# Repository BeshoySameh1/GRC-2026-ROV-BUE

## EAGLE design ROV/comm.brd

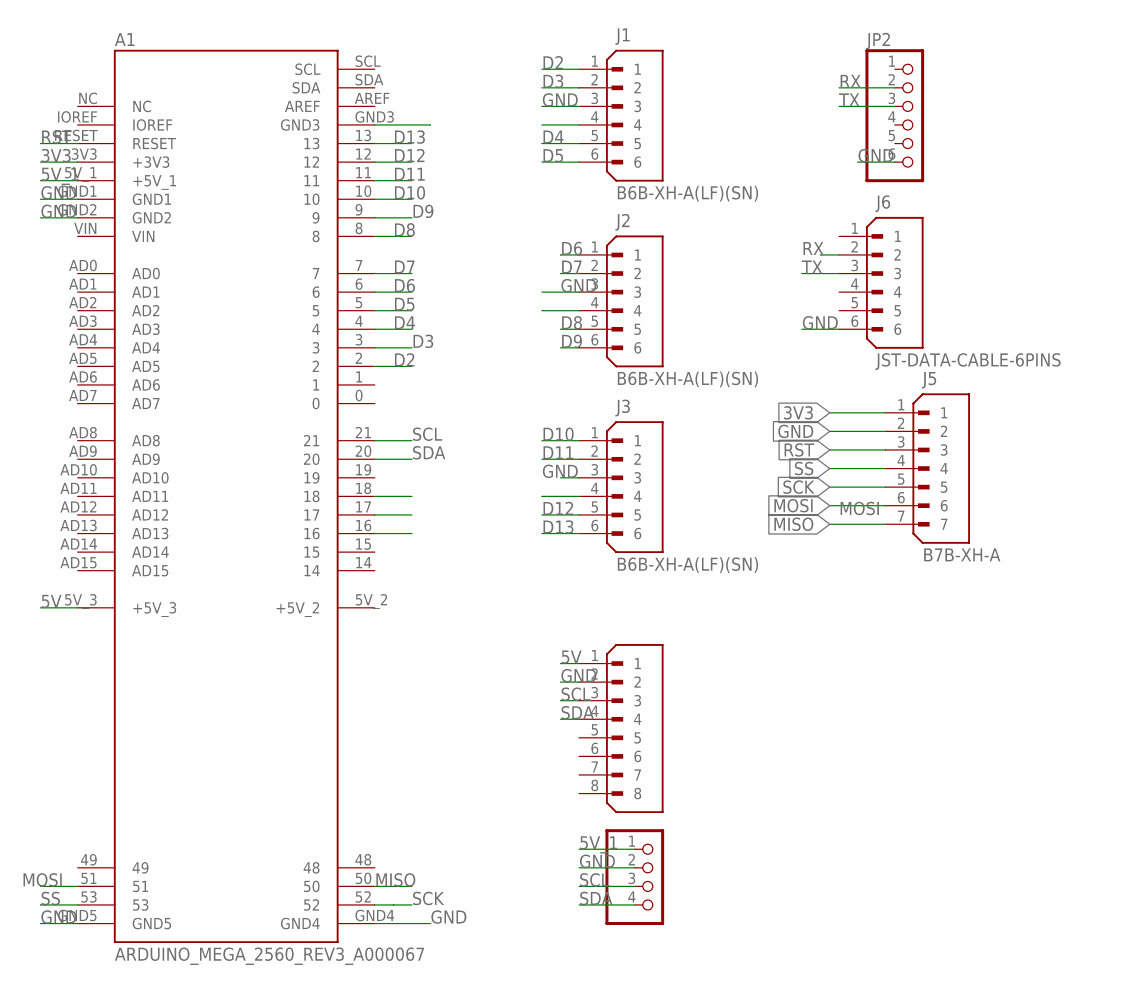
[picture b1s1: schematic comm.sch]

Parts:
A1: ARDUINO_MEGA_2560_REV3_A000067; ARDUINO_ARDUINO_MEGA_2560_REV3_A000067
J1, J2, J3: B6B-XH-A(LF)(SN); JST_B6B-XH-A(LF)(SN)
J4: B8B-XH-A(LF)(SN); JST_B8B-XH-A(LF)(SN)
J5: B7B-XH-A; JST_B7B-XH-A
J6: JST-DATA-CABLE-6PINS; JST_B6B-XH-A(LF)(SN)
JP1: PINHD-1X4; 1X04
JP2: PINHD-1X6; 1X06

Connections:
3V3: A1.3V3 (+3V3), J5.1
5V: A1.5V_3 (+5V_3), J4.1
5V_1: A1.5V_1 (+5V_1), JP1.1
D2: A1.2, J1.1
D3: A1.3, J1.2
D4: A1.4, J1.5
D5: A1.5, J1.6
D6: A1.6, J2.1
D7: A1.7, J2.2
D8: A1.8, J2.5
D9: A1.9, J2.6
D10: A1.10, J3.1
D11: A1.11, J3.2
D12: A1.12, J3.4, J3.5
D13: A1.13, J3.6
GND: A1.GND1, A1.GND2, A1.GND4, A1.GND5, J1.3, J2.3, J3.3, J4.2, J5.2, J6.6, JP1.2, JP2.6
MISO: A1.50, J5.7
MOSI: A1.51, J5.6
RST: A1.RESET, J5.3
RX: J6.2, JP2.2
SCK: A1.52, J5.5
SCL: A1.21, J4.3, JP1.3
SDA: A1.20, J4.4, JP1.4
SS: A1.53, J5.4
TX: J6.3, JP2.3

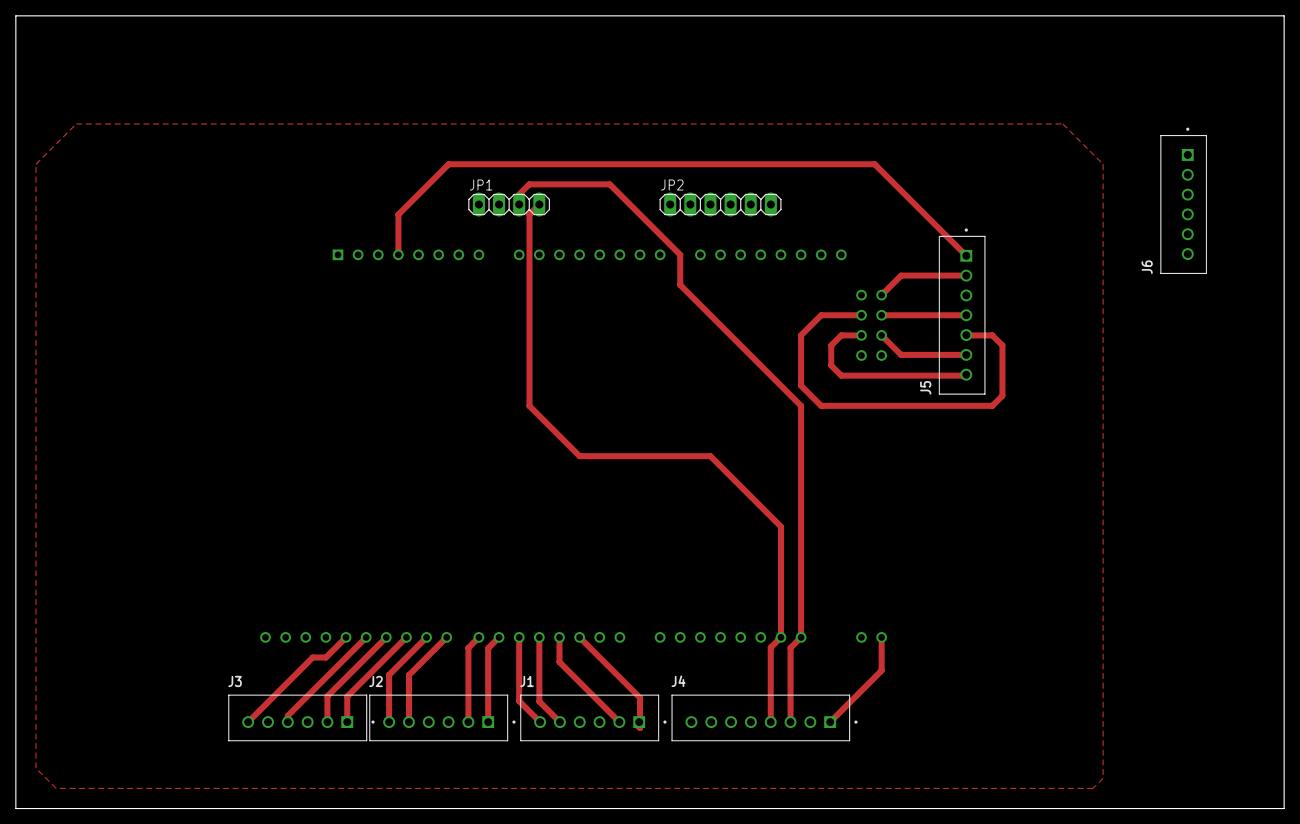
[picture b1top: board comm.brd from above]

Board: 2 copper layers, 160.0 x 100.0 mm, 9 parts (1 on the bottom side), 25 nets.

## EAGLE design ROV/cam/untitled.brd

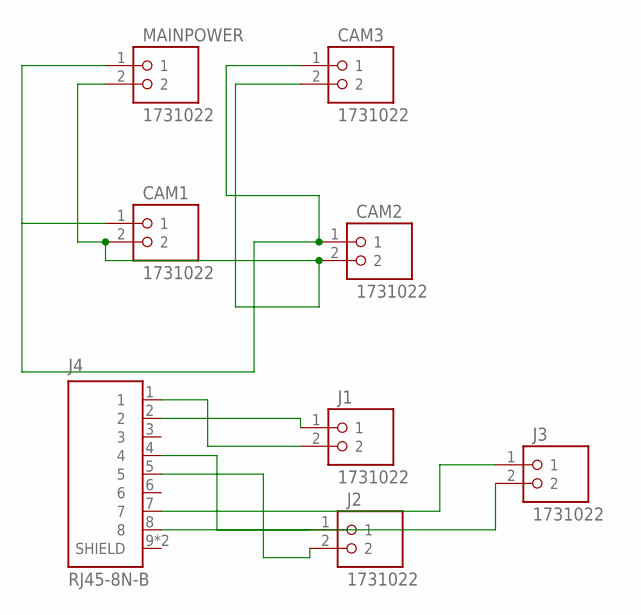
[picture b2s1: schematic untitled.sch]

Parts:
CAM1, CAM2, CAM3: 1731022; PHOENIX_1731022
J1, J2, J3: 1731022; PHOENIX_1731022
J4: RJ45-8N-B; TE_RJ45-8N-B
MAINPOWER: 1731022; PHOENIX_1731022

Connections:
12V: CAM1.1, CAM2.1, CAM3.1, MAINPOWER.1
GND: CAM1.2, CAM2.2, CAM3.2, MAINPOWER.2
unnamed: J1.1, J4.2
unnamed: J1.2, J4.1
unnamed: J2.1, J4.4
unnamed: J2.2, J4.5
unnamed: J3.1, J4.7
unnamed: J3.2, J4.8

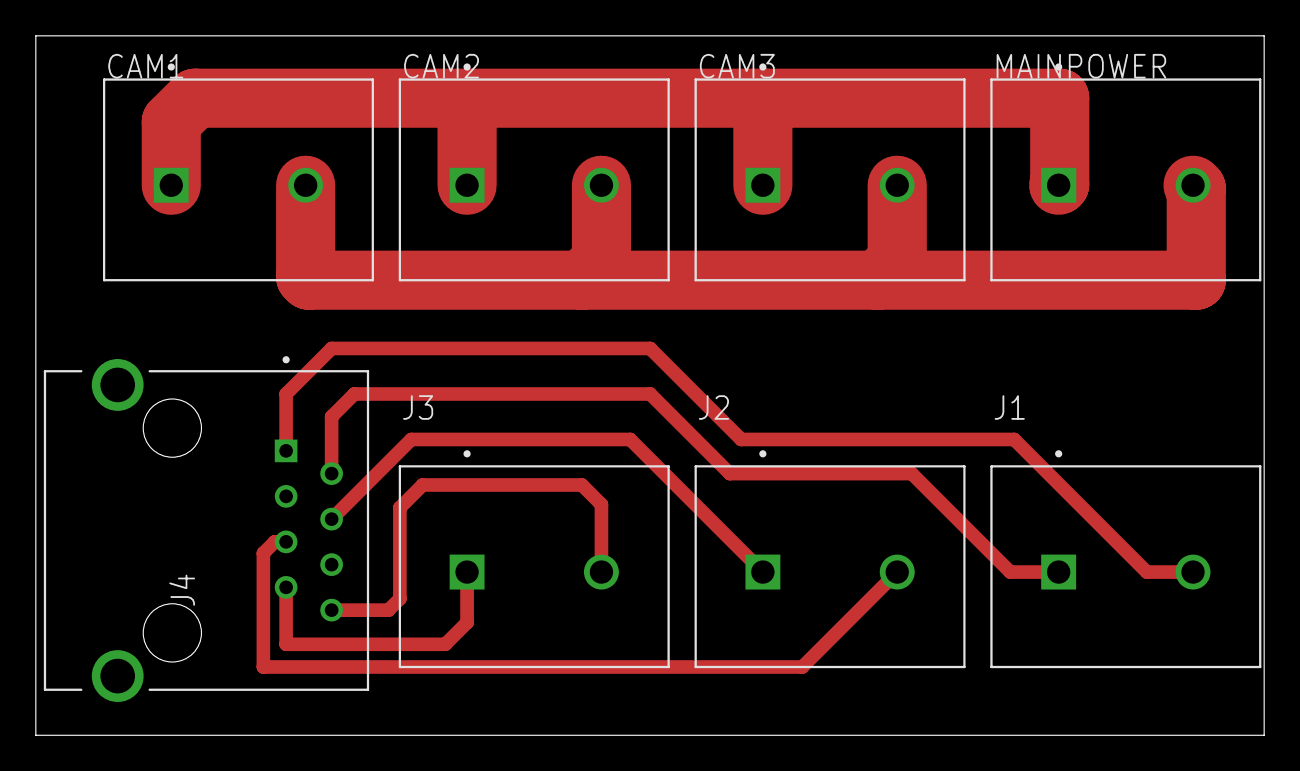
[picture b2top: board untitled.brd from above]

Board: 2 copper layers, 68.6 x 39.0 mm, 8 parts (0 on the bottom side), 8 nets.

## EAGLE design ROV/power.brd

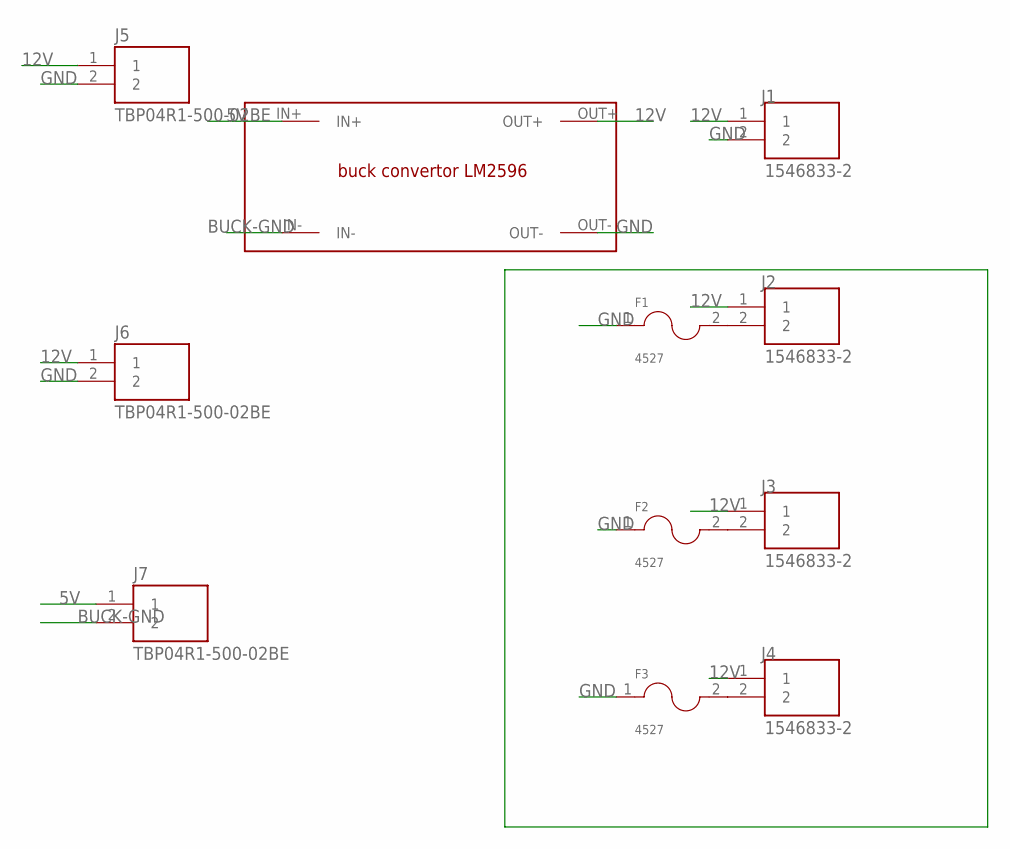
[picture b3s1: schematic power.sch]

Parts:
F1, F2, F3: 4527; FUSE_4527
J1, J2, J3, J4: 1546833-2; TE_1546833-2
J5, J6, J7: TBP04R1-500-02BE; CUI_TBP04R1-500-02BE
U$1: LM2596

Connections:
5V: J7.1, U$1.IN+
12V: J1.1, J2.1, J3.1, J4.1, J5.1, J6.1, U$1.OUT+
BUCK-GND: J7.2, U$1.IN-
GND: F1.1, F2.1, F3.1, J1.2, J5.2, J6.2, U$1.OUT-
unnamed: F1.2, J2.2
unnamed: F2.2, J3.2
unnamed: F3.2, J4.2

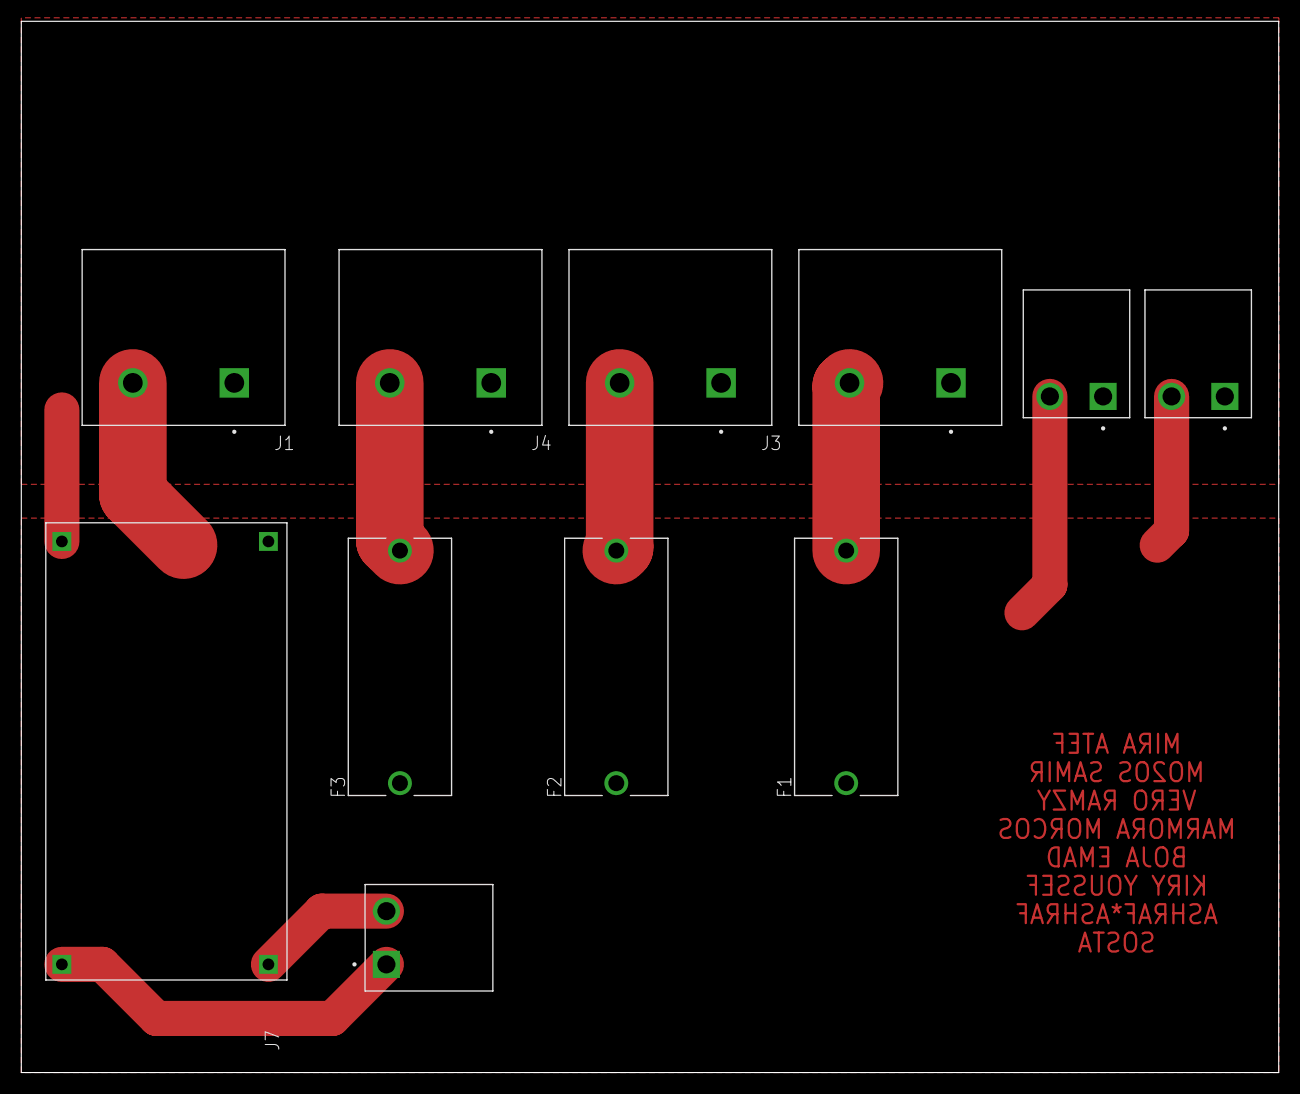
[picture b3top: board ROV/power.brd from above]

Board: 2 copper layers, 118.1 x 98.7 mm, 11 parts (0 on the bottom side), 7 nets.

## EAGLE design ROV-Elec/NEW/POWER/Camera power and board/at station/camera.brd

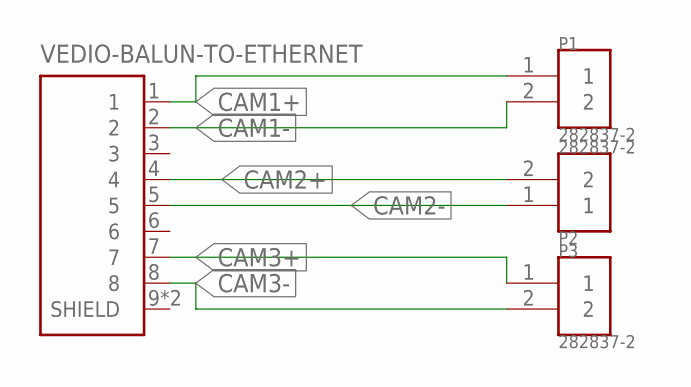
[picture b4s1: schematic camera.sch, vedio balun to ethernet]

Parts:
P1, P2, P3: 282837-2; TE_282837-2
VEDIO-BALUN-TO-ETHERNET: RJ45-8N-B; TE_RJ45-8N-B

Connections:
CAM1+: P1.1, VEDIO-BALUN-TO-ETHERNET.1
CAM1-: P1.2, VEDIO-BALUN-TO-ETHERNET.2
CAM2+: P2.2, VEDIO-BALUN-TO-ETHERNET.4
CAM2-: P2.1, VEDIO-BALUN-TO-ETHERNET.5
CAM3+: P3.1, VEDIO-BALUN-TO-ETHERNET.7
CAM3-: P3.2, VEDIO-BALUN-TO-ETHERNET.8

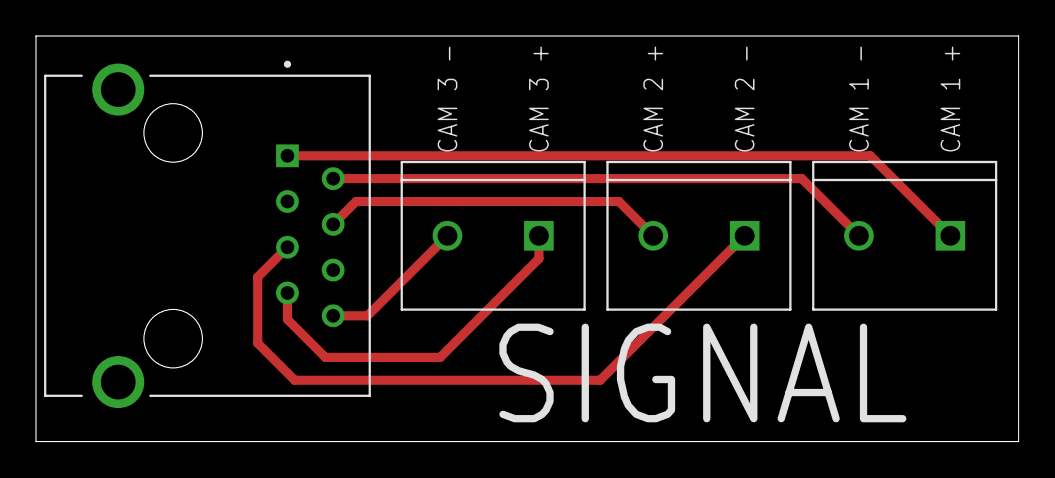
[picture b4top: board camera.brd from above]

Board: 2 copper layers, 54.6 x 22.5 mm, 4 parts (0 on the bottom side), 6 nets.

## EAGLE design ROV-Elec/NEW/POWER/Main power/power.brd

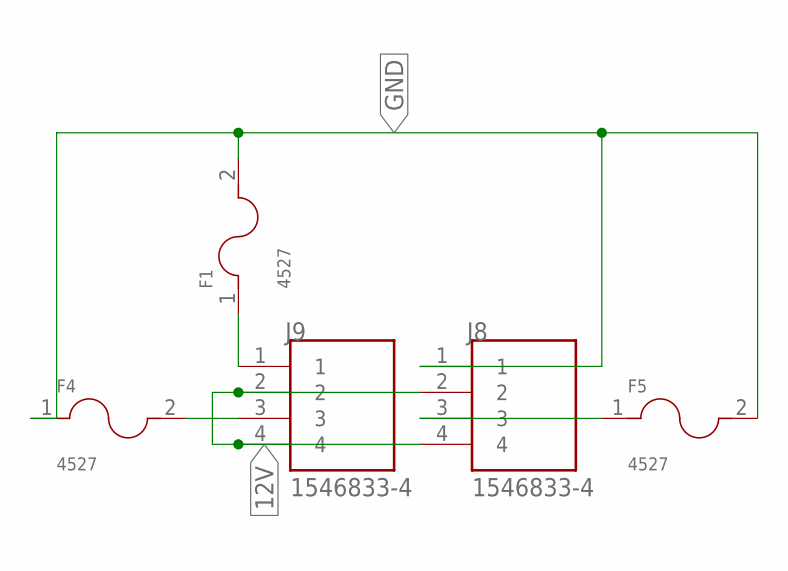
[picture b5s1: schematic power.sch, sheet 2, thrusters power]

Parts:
F1, F4, F5: 4527; FUSE_4527
J8, J9: 1546833-4; TE_1546833-4

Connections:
12V: J8.2, J8.4, J9.2, J9.4; also elsewhere on the board
GND: F1.2, F4.1, F5.2, J8.1; also elsewhere on the board
unnamed: F4.2, J9.3
unnamed: F5.1, J8.3
unnamed: F1.1, J9.1

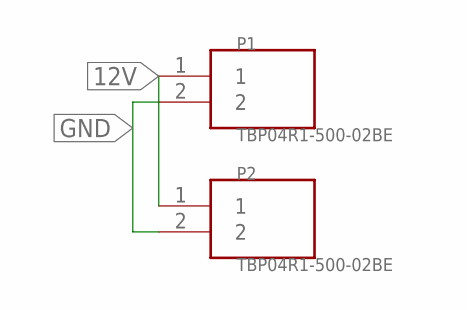
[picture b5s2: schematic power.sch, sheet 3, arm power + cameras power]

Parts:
P1, P2: TBP04R1-500-02BE; CUI_TBP04R1-500-02BE

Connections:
12V: P1.1, P2.1; also elsewhere on the board
GND: P1.2, P2.2; also elsewhere on the board

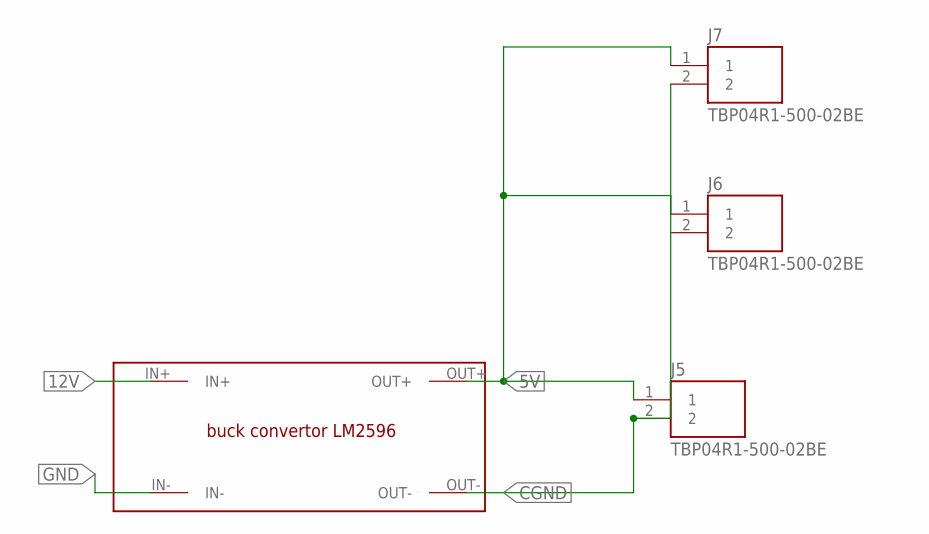
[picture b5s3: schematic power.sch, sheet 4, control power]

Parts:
J5, J6, J7: TBP04R1-500-02BE; CUI_TBP04R1-500-02BE
U$1: LM2596

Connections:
5V: J5.1, J6.1, J7.1, U$1.OUT+
12V: U$1.IN+; also elsewhere on the board
CGND: J5.2, J6.2, J7.2, U$1.OUT-
GND: U$1.IN-; also elsewhere on the board

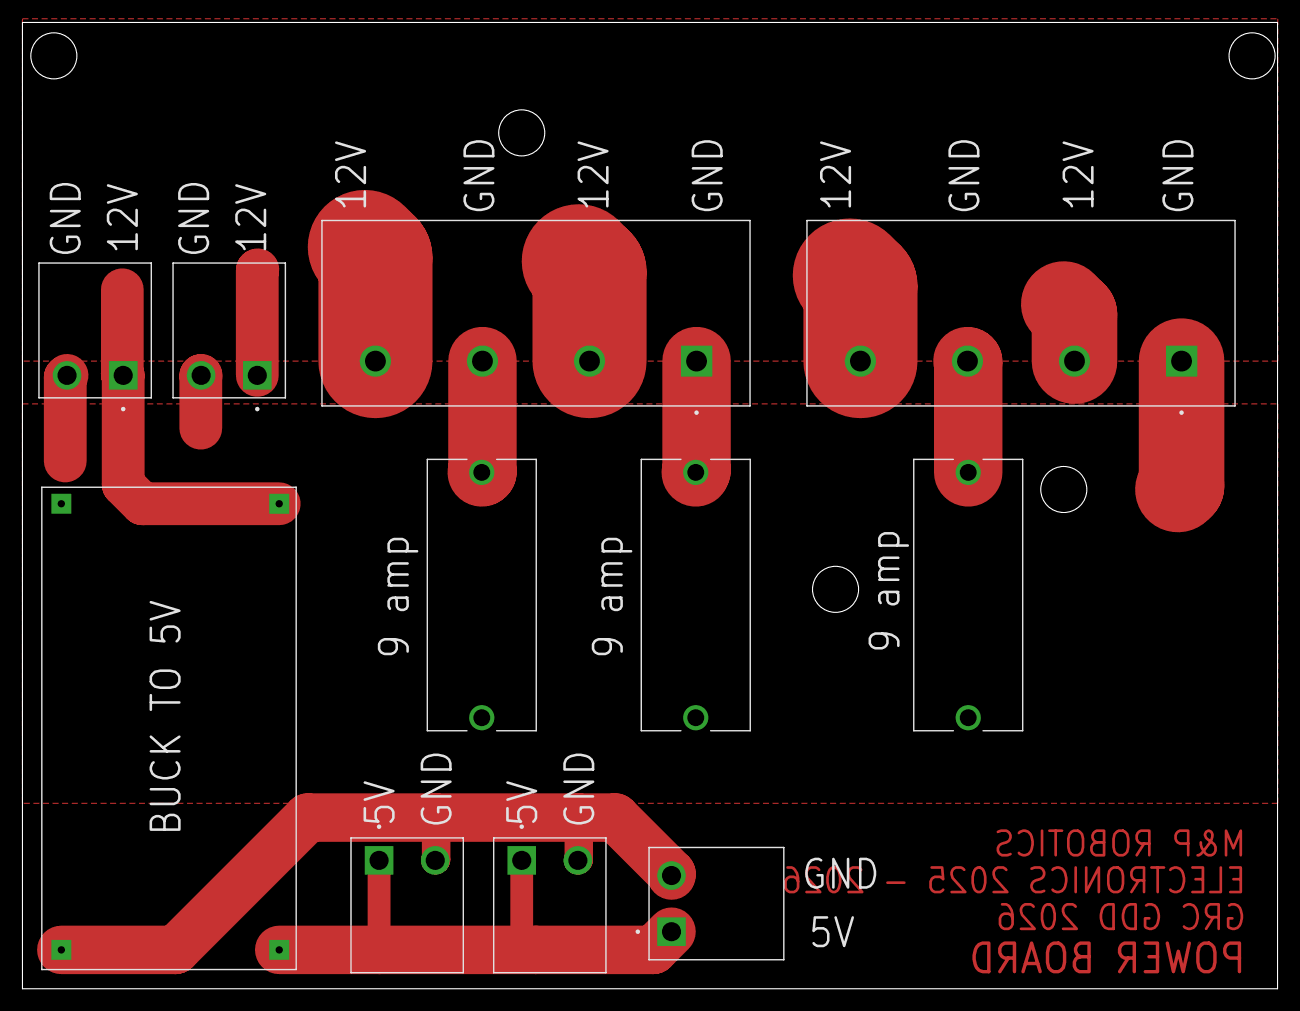
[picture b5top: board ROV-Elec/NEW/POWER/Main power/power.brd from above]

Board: 2 copper layers, 111.7 x 86.0 mm, 11 parts (0 on the bottom side), 7 nets.

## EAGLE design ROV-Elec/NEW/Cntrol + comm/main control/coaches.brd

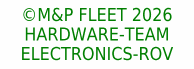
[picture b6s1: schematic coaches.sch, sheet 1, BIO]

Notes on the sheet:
©M&P FLEET 2026 HARDWARE-TEAM ELECTRONICS-ROV

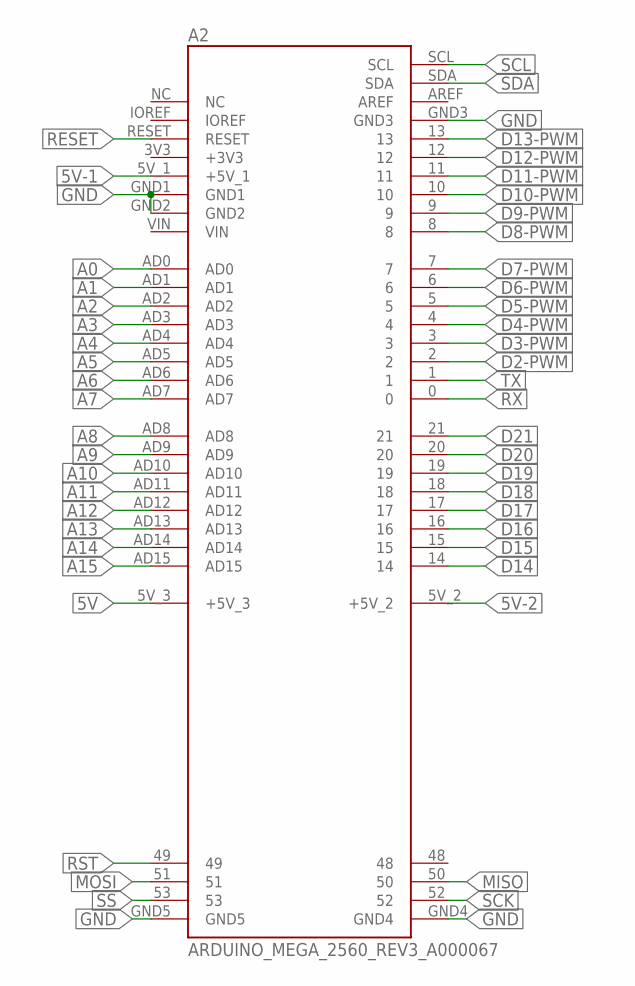
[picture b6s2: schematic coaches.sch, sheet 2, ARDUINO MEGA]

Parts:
A2: ARDUINO_MEGA_2560_REV3_A000067; ARDUINO_ARDUINO_MEGA_2560_REV3_A000067

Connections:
5V: A2.5V_3 (+5V_3); also elsewhere on the board
5V-1: A2.5V_1 (+5V_1); also elsewhere on the board
5V-2: A2.5V_2 (+5V_2)
A0: A2.AD0
A1: A2.AD1
A2: A2.AD2
A3: A2.AD3
A4: A2.AD4
A5: A2.AD5
A6: A2.AD6
A7: A2.AD7; also elsewhere on the board
A8: A2.AD8
A9: A2.AD9
A10: A2.AD10
A11: A2.AD11
A12: A2.AD12
A13: A2.AD13
A14: A2.AD14
A15: A2.AD15
D2-PWM: A2.2; also elsewhere on the board
D3-PWM: A2.3; also elsewhere on the board
D4-PWM: A2.4; also elsewhere on the board
D5-PWM: A2.5; also elsewhere on the board
D6-PWM: A2.6; also elsewhere on the board
D7-PWM: A2.7; also elsewhere on the board
D8-PWM: A2.8; also elsewhere on the board
D9-PWM: A2.9; also elsewhere on the board
D10-PWM: A2.10; also elsewhere on the board
D11-PWM: A2.11; also elsewhere on the board
D12-PWM: A2.12; also elsewhere on the board
D13-PWM: A2.13; also elsewhere on the board
D14: A2.14; also elsewhere on the board
D15: A2.15; also elsewhere on the board
D16: A2.16; also elsewhere on the board
D17: A2.17; also elsewhere on the board
D18: A2.18; also elsewhere on the board
D19: A2.19
D20: A2.20; also elsewhere on the board
D21: A2.21; also elsewhere on the board
GND: A2.GND1, A2.GND2, A2.GND3, A2.GND4, A2.GND5; also elsewhere on the board
MISO: A2.50; also elsewhere on the board
MOSI: A2.51; also elsewhere on the board
RESET: A2.RESET
RST: A2.49; also elsewhere on the board
RX: A2.0; also elsewhere on the board
SCK: A2.52; also elsewhere on the board
SCL: A2.SCL
SDA: A2.SDA
SS: A2.53; also elsewhere on the board
TX: A2.1; also elsewhere on the board

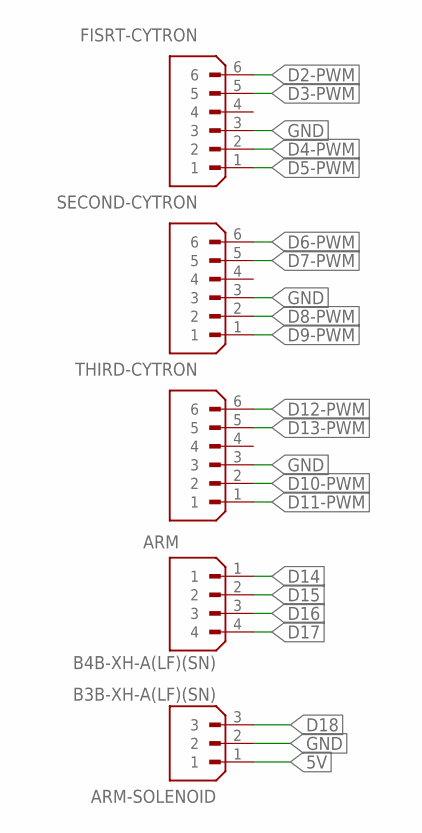
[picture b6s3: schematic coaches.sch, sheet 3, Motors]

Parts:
ARM: B4B-XH-A(LF)(SN); JST_B4B-XH-A(LF)(SN)
ARM-SOLENOID: B3B-XH-A(LF)(SN); JST_B3B-XH-A(LF)(SN)
FISRT-CYTRON: B6B-XH-A(LF)(SN); JST_B6B-XH-A(LF)(SN)
SECOND-CYTRON: B6B-XH-A(LF)(SN); JST_B6B-XH-A(LF)(SN)
THIRD-CYTRON: B6B-XH-A(LF)(SN); JST_B6B-XH-A(LF)(SN)

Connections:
5V: ARM-SOLENOID.1; also elsewhere on the board
D2-PWM: FISRT-CYTRON.6; also elsewhere on the board
D3-PWM: FISRT-CYTRON.5; also elsewhere on the board
D4-PWM: FISRT-CYTRON.2; also elsewhere on the board
D5-PWM: FISRT-CYTRON.1; also elsewhere on the board
D6-PWM: SECOND-CYTRON.6; also elsewhere on the board
D7-PWM: SECOND-CYTRON.5; also elsewhere on the board
D8-PWM: SECOND-CYTRON.2; also elsewhere on the board
D9-PWM: SECOND-CYTRON.1; also elsewhere on the board
D10-PWM: THIRD-CYTRON.2; also elsewhere on the board
D11-PWM: THIRD-CYTRON.1; also elsewhere on the board
D12-PWM: THIRD-CYTRON.6; also elsewhere on the board
D13-PWM: THIRD-CYTRON.5; also elsewhere on the board
D14: ARM.1; also elsewhere on the board
D15: ARM.2; also elsewhere on the board
D16: ARM.3; also elsewhere on the board
D17: ARM.4; also elsewhere on the board
D18: ARM-SOLENOID.3; also elsewhere on the board
GND: ARM-SOLENOID.2, FISRT-CYTRON.3, SECOND-CYTRON.3, THIRD-CYTRON.3; also elsewhere on the board

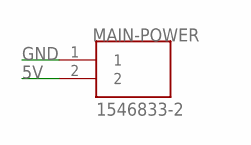
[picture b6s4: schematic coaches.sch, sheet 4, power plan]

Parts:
MAIN-POWER: 1546833-2; TE_1546833-2

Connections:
5V: MAIN-POWER.2; also elsewhere on the board
GND: MAIN-POWER.1; also elsewhere on the board

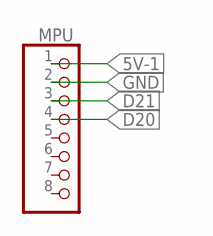
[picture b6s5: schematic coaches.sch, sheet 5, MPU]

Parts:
MPU: PINHD-1X8; 1X08

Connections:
5V-1: MPU.1; also elsewhere on the board
D20: MPU.4; also elsewhere on the board
D21: MPU.3; also elsewhere on the board
GND: MPU.2; also elsewhere on the board

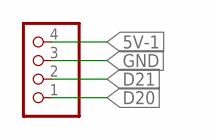
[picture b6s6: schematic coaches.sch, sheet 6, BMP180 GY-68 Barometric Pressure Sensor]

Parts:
PROMETER: PINHD-1X4; 1X04

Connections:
5V-1: PROMETER.4; also elsewhere on the board
D20: PROMETER.1; also elsewhere on the board
D21: PROMETER.2; also elsewhere on the board
GND: PROMETER.3; also elsewhere on the board

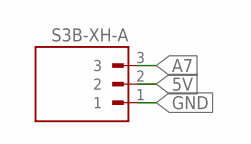
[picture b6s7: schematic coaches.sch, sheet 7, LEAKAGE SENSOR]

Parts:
J3: S3B-XH-A; JST_S3B-XH-A

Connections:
5V: J3.2; also elsewhere on the board
A7: J3.3; also elsewhere on the board
GND: J3.1; also elsewhere on the board

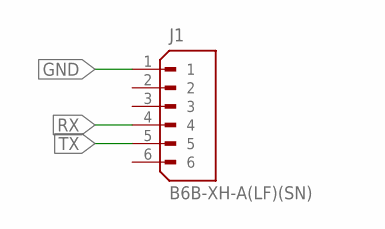
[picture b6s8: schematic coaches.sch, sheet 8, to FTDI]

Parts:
J1: B6B-XH-A(LF)(SN); JST_B6B-XH-A(LF)(SN)

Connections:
GND: J1.1; also elsewhere on the board
RX: J1.4; also elsewhere on the board
TX: J1.5; also elsewhere on the board

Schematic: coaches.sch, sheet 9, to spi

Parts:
J2, J4: B6B-XH-A(LF)(SN); JST_B6B-XH-A(LF)(SN)
SPI-POWER: PINHD-1X3; 1X03

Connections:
3V3: J4.4, SPI-POWER.2
5V: SPI-POWER.1; also elsewhere on the board
GND: J2.1, J2.2, J4.6, SPI-POWER.3; also elsewhere on the board
MISO: J4.1; also elsewhere on the board
MOSI: J2.3; also elsewhere on the board
RST: J4.2; also elsewhere on the board
SCK: J2.4; also elsewhere on the board
SS: J2.5; also elsewhere on the board
